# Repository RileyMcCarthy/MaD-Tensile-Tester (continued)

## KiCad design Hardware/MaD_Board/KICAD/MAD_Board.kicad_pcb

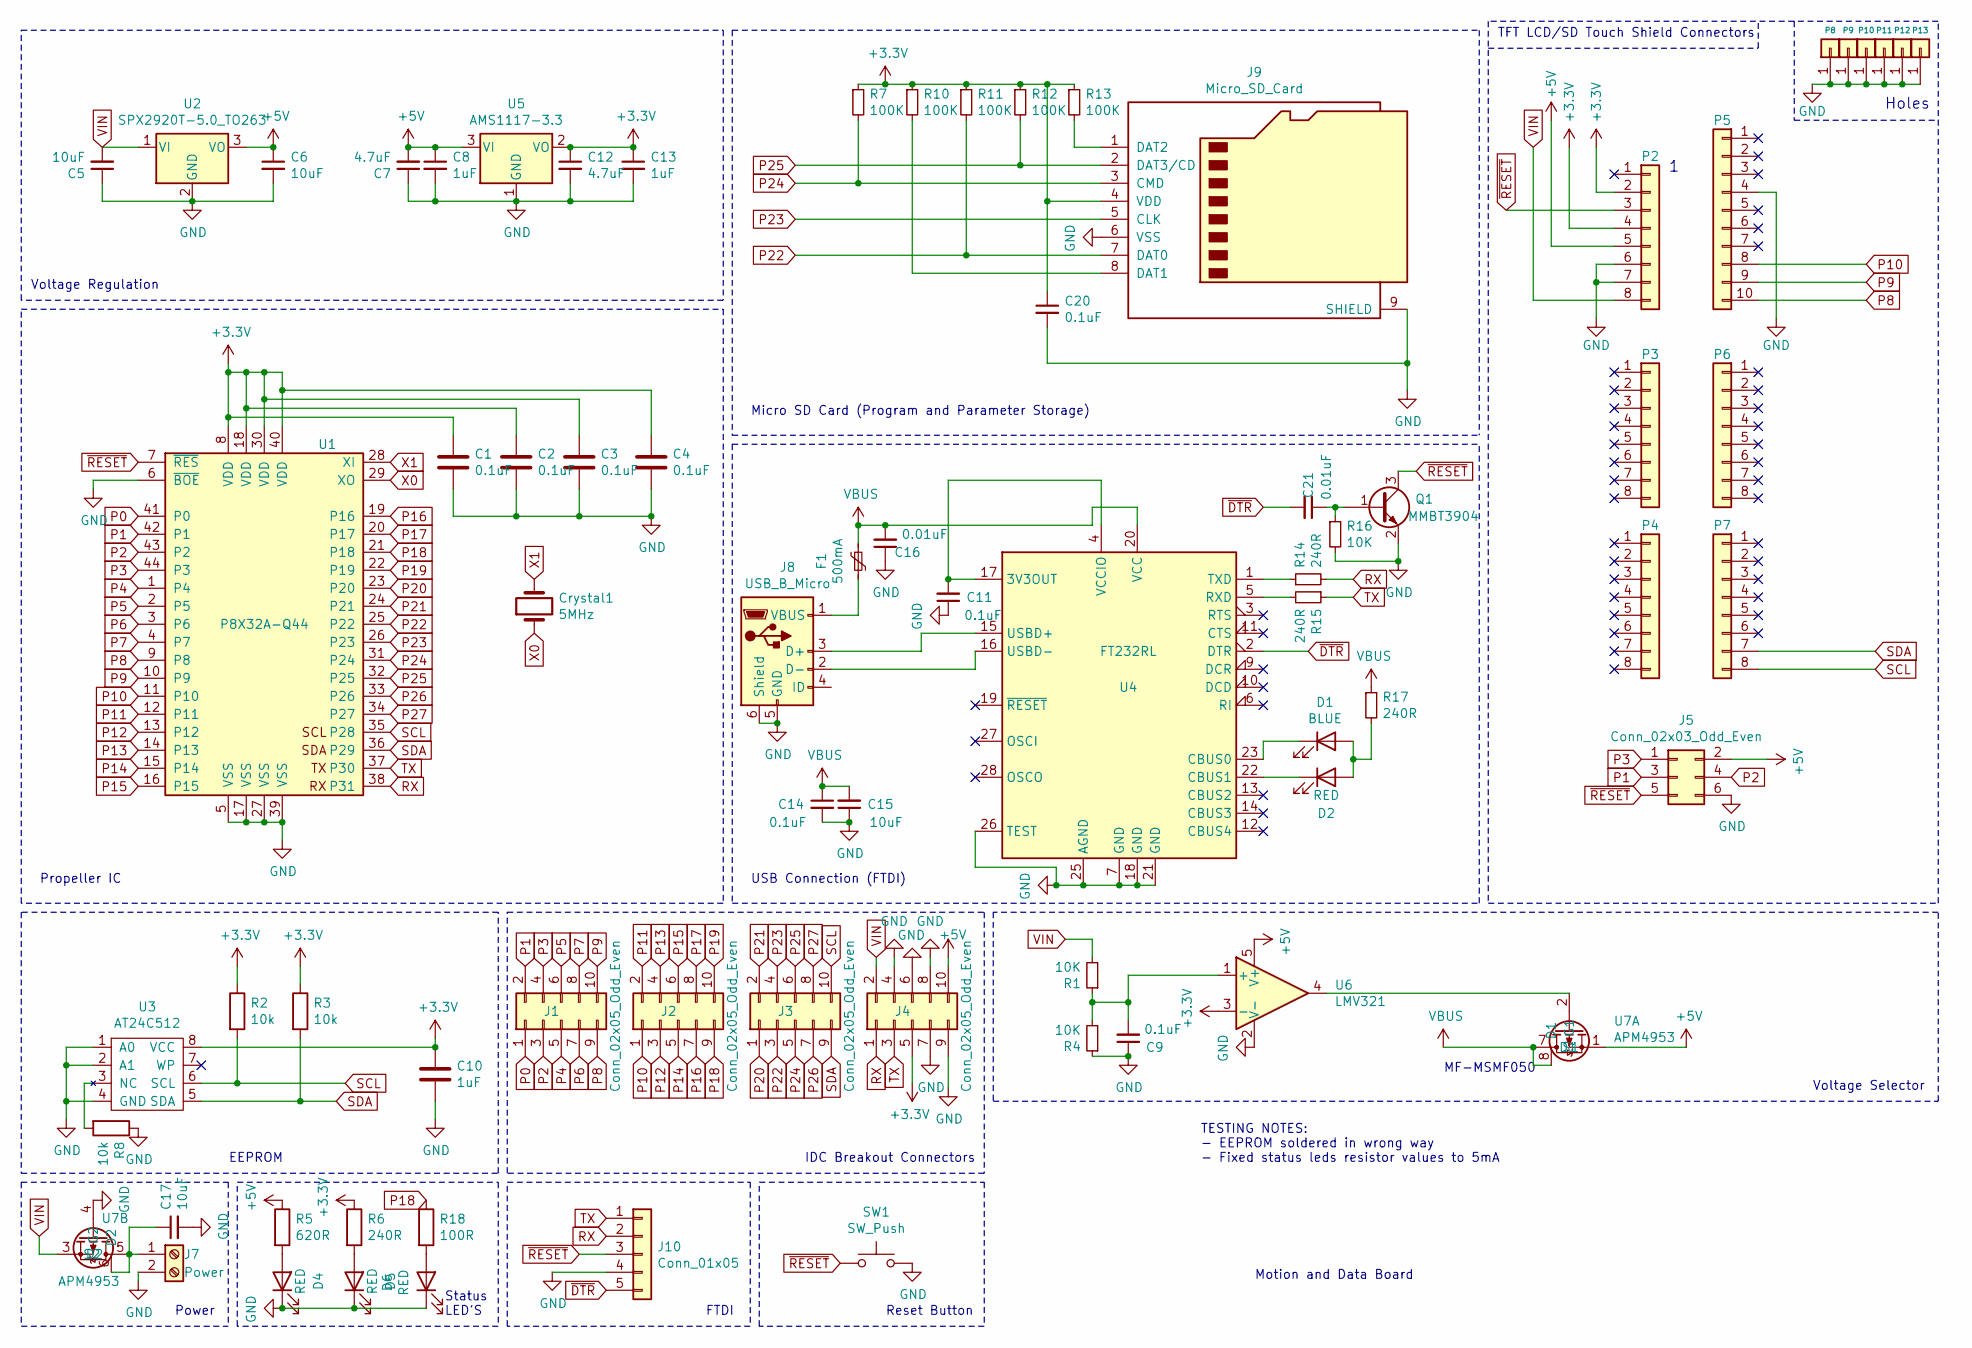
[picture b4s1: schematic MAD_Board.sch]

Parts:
C1, C2, C3, C4, C9, C11, C14, C20: 0.1uF; C_0603_1608Metric; LCSC Part # C14663
C5, C6, C15, C17: 10uF; C_0805_2012Metric; LCSC Part # C15850
C7, C12: 4.7uF; C_0603_1608Metric; LCSC Part # C14663
C8, C10, C13: 1uF; C_0603_1608Metric; LCSC Part # C15849
C16, C21: 0.01uF; C_0603_1608Metric; LCSC Part # C57112
Crystal1: 5MHz; Crystal_HC49-U_Vertical; LCSC Part # C2198
D1: BLUE; LED_0603_1608Metric; LCSC Part # C72041
D2, D4, D5, D6: RED; LED_0603_1608Metric; LCSC Part # C84256
F1: 500mA; Fuse_0603_1608Metric; LCSC Part # C210356
J1, J2, J3, J4: Conn_02x05_Odd_Even; IDC-Header_2x05_P2.54mm_Vertical
J5: Conn_02x03_Odd_Even; PinHeader_2x03_P2.54mm_Vertical
J7: Power; TerminalBlock_bornier-2_P5.08mm
J8: USB_B_Micro; USB_Micro-AB_Molex_47590-0001; LCSC Part # C404969
J9: Micro_SD_Card; microSD_HC_Hirose_DM3D-SF; LCSC Part # C719027
J10: Conn_01x05; PinHeader_1x05_P2.54mm_Vertical
P2: Power; Socket_Strip_Arduino_1x08
P3, P4: Analog; Socket_Strip_Arduino_1x08
P5: PWM; Socket_Strip_Arduino_1x10
P6: PWM; Socket_Strip_Arduino_1x08
P7: Communication; Socket_Strip_Arduino_1x08
P8, P9, P10, P11, P12, P13: CONN_01X01; Arduino_1pin
Q1: MMBT3904; SOT-23; LCSC Part # C20526
R1, R4, R16: 10K; R_0603_1608Metric; LCSC Part # C25804
R2, R3, R8: 10k; R_0603_1608Metric; LCSC Part # C25804
R5: 620R; R_0603_1608Metric; LCSC Part # C23220
R6, R14, R15, R17: 240R; R_0603_1608Metric; LCSC Part # C25221
R7, R10, R11, R12, R13: 100K; R_0603_1608Metric; LCSC Part # C25803
R18: 100R; R_0603_1608Metric; LCSC Part # C22775
SW1: SW_Push; LED_1210_3225Metric
U1: P8X32A-Q44; LQFP-44_10x10mm_P0.8mm
U2: SPX2920T-5.0_TO263; TO-263-3_TabPin2; LCSC Part # C24592
U3: AT24C512; SOIC-8-1EP_3.9x4.9mm_P1.27mm_EP2.514x3.2mm; LCSC Part # C6482
U4: FT232RL; SSOP-28_5.3x10.2mm_P0.65mm; LCSC Part # C8690
U5: AMS1117-3.3; SOT-223-3_TabPin2; LCSC Part # C6186
U6: LMV321; SOT-23-5; LCSC Part # C7972
U7: APM4953; SOP-8_3.9x4.9mm_P1.27mm; LCSC Part # C20897

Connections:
+3V3: C1.1, C2.1, C3.1, C4.1, C10.1, C12.1, C13.1, C20.1, J4.5, J9.4 (VDD), P2.2, P2.4, R2.1, R3.1, R6.1, R7.1, R10.1, R11.1, R12.1, R13.1, U1.8 (VDD), U1.18 (VDD), U1.30 (VDD), U1.40 (VDD), U3.8 (VCC), U5.2 (VO), U6.3 (-)
+5V: C6.1, C7.2, C8.1, J4.10, J5.2, P2.5, R5.1, U2.3 (VO), U5.3 (VI), U6.5 (V+), U7.1 (S1)
GND: C1.2, C2.2, C3.2, C4.2, C5.1, C6.2, C7.1, C8.2, C9.1, C10.2, C11.1, C12.2, C13.2, C14.2, C15.1, C16.1, C17.2, C20.2, D4.1 (K), D5.1 (K), D6.1 (K), J4.4, J4.6, J4.7, J4.8, J4.9, J5.6, J7.2, J8.5 (GND), J8.6 (Shield), J9.6 (VSS), J9.9 (SHIELD), J10.4, P2.6, P2.7, P5.4, P8.1, P9.1, P10.1, P11.1, P12.1, P13.1, Q1.2 (E), R4.1, R8.1, R16.2, SW1.2, U1.5 (VSS), U1.6 (~BOE), U1.17 (VSS), U1.27 (VSS), U1.39 (VSS), U2.2 (GND), U3.1 (A0), U3.2 (A1), U3.4 (GND), U4.7 (GND), U4.18 (GND), U4.21 (GND), U4.25 (AGND), U4.26 (TEST), U5.1 (GND), U6.2 (V-), U7.4 (G2)
unnamed: C9.2, R1.1, R4.2, U6.1 (+)
unnamed: C11.2, U4.4 (VCCIO), U4.17 (3V3OUT)
unnamed: C17.1, J7.1, U7.5 (D2), U7.6 (D2)
unnamed: C21.1, Q1.1 (B), R16.1
unnamed: D1.1 (K), U4.23 (CBUS0)
unnamed: D1.2 (A), D2.2 (A), R17.2
unnamed: D2.1 (K), U4.22 (CBUS1)
unnamed: D4.2 (A), R5.2
unnamed: D5.2 (A), R6.2
unnamed: D6.2 (A), R18.2
unnamed: F1.2, J8.1 (VBUS)
unnamed: J8.2 (D-), U4.16 (USBD-)
unnamed: J8.3 (D+), U4.15 (USBD+)
unnamed: J9.1 (DAT2), R13.2
unnamed: J9.8 (DAT1), R10.2
unnamed: R8.2, U3.3 (NC)
unnamed: R14.1, U4.1 (TXD)
unnamed: R15.2, U4.5 (RXD)
unnamed: U6.4, U7.2 (G1)
P0: J1.1, P6.8, U1.41 (P0)
P1: J1.2, J5.3, P6.7, U1.42 (P1)
P2: J1.3, J5.4, P6.6, U1.43 (P2)
P3: J1.4, J5.1, P6.5, U1.44 (P3)
P4: J1.5, P6.4, U1.1 (P4)
P5: J1.6, P6.3, U1.2 (P5)
P6: J1.7, P6.2, U1.3 (P6)
P7: J1.8, P6.1, U1.4 (P7)
P8: J1.9, P5.10, U1.9 (P8)
P9: J1.10, P5.9, U1.10 (P9)
P10: J2.1, P5.8, U1.11 (P10)
P11: J2.2, P5.7, U1.12 (P11)
P12: J2.3, P5.6, U1.13 (P12)
P13: J2.4, P5.5, U1.14 (P13)
P14: J2.5, P5.2, U1.15 (P14)
P15: J2.6, P5.1, U1.16 (P15)
P16: J2.7, U1.19 (P16)
P17: J2.8, U1.20 (P17)
P18: J2.9, R18.1, U1.21 (P18)
P19: J2.10, U1.22 (P19)
P20: J3.1, U1.23 (P20)
P21: J3.2, U1.24 (P21)
P22: J3.3, J9.7 (DAT0), R11.2, U1.25 (P22)
P23: J3.4, J9.5 (CLK), U1.26 (P23)
P24: J3.5, J9.3 (CMD), R7.2, U1.31 (P24)
P25: J3.6, J9.2 (DAT3/CD), R12.2, U1.32 (P25)
P26: J3.7, U1.33 (P26)
P27: J3.8, U1.34 (P27)
RX: J4.1, J10.2, R14.2, U1.38 (P31)
SCL: J3.10, P7.8, R2.2, U1.35 (P28), U3.6 (SCL)
SDA: J3.9, P7.7, R3.2, U1.36 (P29), U3.5 (SDA)
TX: J4.3, J10.1, R15.1, U1.37 (P30)
VBUS: C14.1, C15.2, C16.2, F1.1, R17.1, U4.20 (VCC), U7.7 (D1), U7.8 (D1)
VSS: C5.2, J4.2, P2.8, R1.2, U2.1 (VI), U7.3 (S2)
X0: Crystal1.1, U1.29 (XO)
X1: Crystal1.2, U1.28 (XI)
~DTR: C21.2, J10.5, U4.2 (DTR)
~RESET: J5.5, J10.3, P2.3, Q1.3 (C), SW1.1, U1.7 (~RES)

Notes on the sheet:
Holes
EEPROM
Propeller IC
USB Connection (FTDI)
Power
IDC Breakout Connectors
TFT LCD/SD Touch Shield Connectors
Motion and Data Board
MF-MSMF050
Voltage Selector
Micro SD Card (Program and Parameter Storage)
Voltage Regulation
FTDI
Reset Button
Status LED'S
TESTING NOTES: - EEPROM soldered in wrong way - Fixed status leds resistor values to 5mA

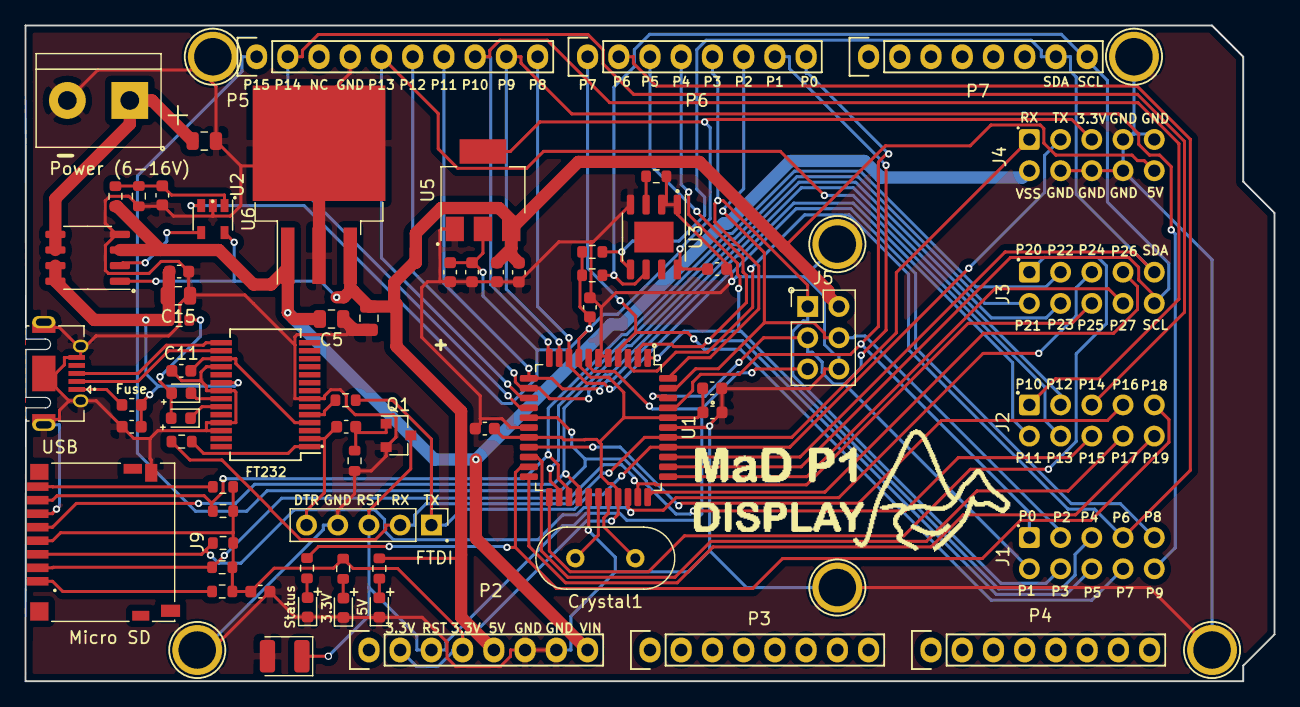
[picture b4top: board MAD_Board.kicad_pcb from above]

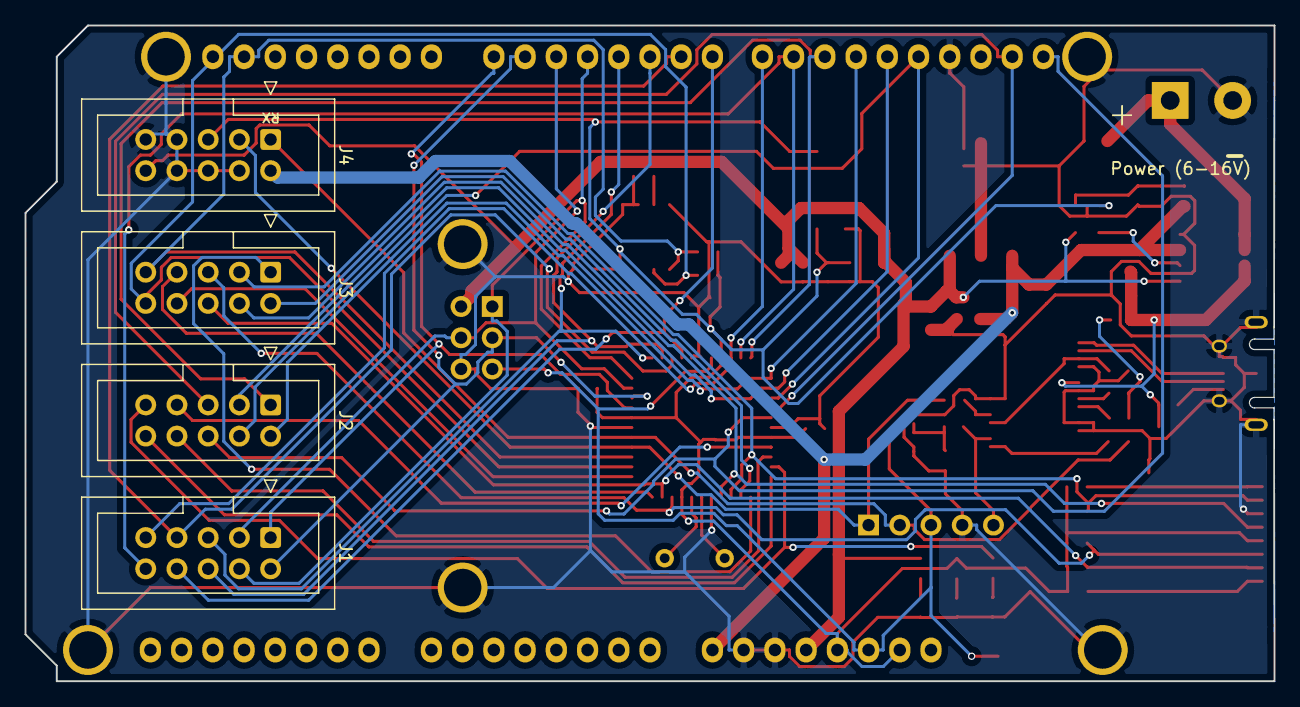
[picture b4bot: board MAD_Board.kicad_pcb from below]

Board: 2 copper layers, 101.6 x 53.3 mm, 74 parts (4 on the bottom side), 60 nets.

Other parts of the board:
LOGO: LOGO9

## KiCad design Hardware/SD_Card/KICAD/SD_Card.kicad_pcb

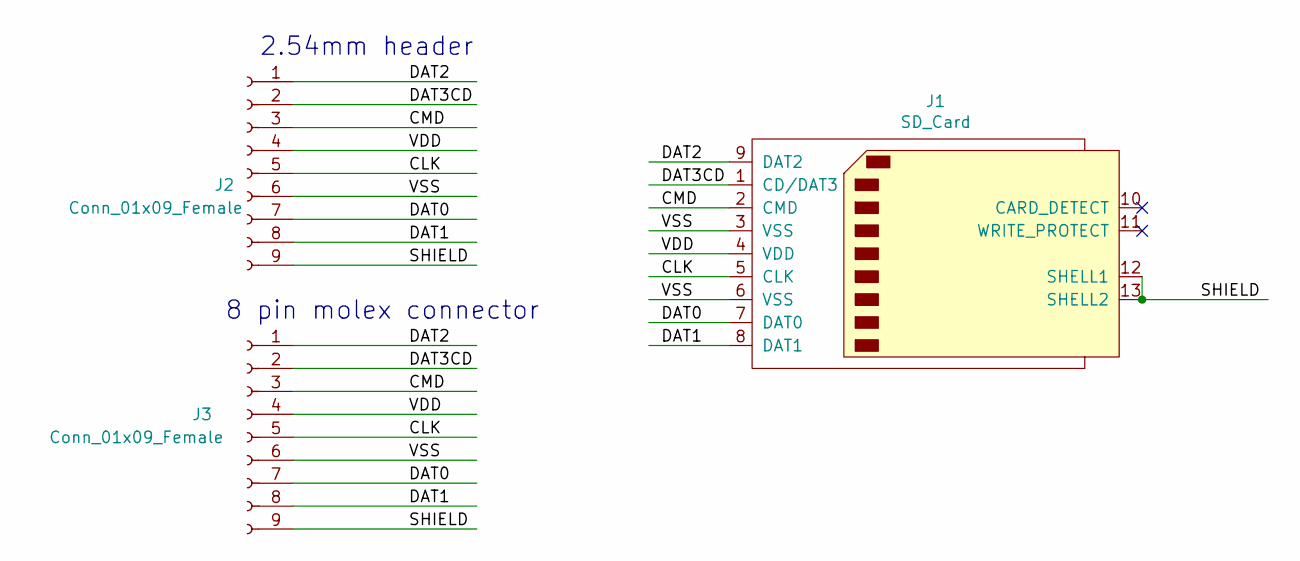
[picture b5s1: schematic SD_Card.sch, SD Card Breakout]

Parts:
J1: SD_Card; 609-3956-2-ND
J2: Conn_01x09_Female; WM26501
J3: Conn_01x09_Female; PinHeader_1x09_P2.54mm_Vertical

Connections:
/CLK: J1.5 (CLK), J2.5, J3.5
/CMD: J1.2 (CMD), J2.3, J3.3
/DAT0: J1.7 (DAT0), J2.7, J3.7
/DAT1: J1.8 (DAT1), J2.8, J3.8
/DAT2: J1.9 (DAT2), J2.1, J3.1
/DAT3CD: J1.1 (CD/DAT3), J2.2, J3.2
/SHIELD: J1.12 (SHELL1), J1.13 (SHELL2), J2.9, J3.9
/VDD: J1.4 (VDD), J2.4, J3.4
/VSS: J1.3 (VSS), J1.6 (VSS), J2.6, J3.6

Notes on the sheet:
2.54mm header
8 pin molex connector

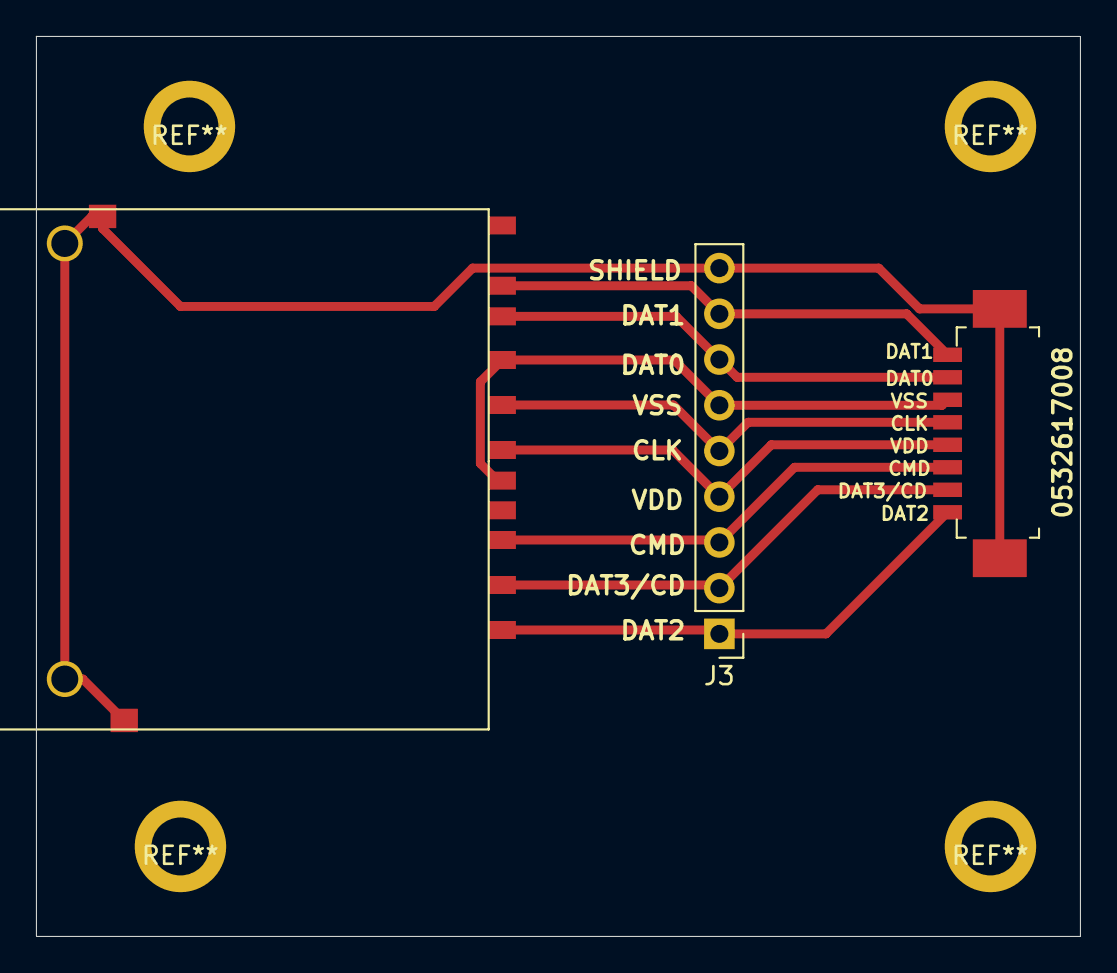
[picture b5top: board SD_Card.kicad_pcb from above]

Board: 2 copper layers, 58.0 x 50.0 mm, 3 parts (0 on the bottom side), 9 nets.

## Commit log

2021-04-02 init commit
2021-04-17 Merging all tensile testing machine related repositorys into a single repo
2021-04-18 Added MaD Firmware to repo
2021-04-24 Updated MaD_Firmware with demo code, issues with stack overflow will be updating soon
2021-04-24 Updated MaD_Firmware with demo code.Has some issues with stack overflow
2021-04-24 Updated MaD_Firmware with demo. Current contains stack overflow issues
2021-04-26 Updating comments
2021-04-27 Removed duplicate Tensile Board folder
2021-04-27 change state machine from c++ to c
2021-04-29 using libpropeller for forcegauge
2021-04-29 Updating force gauge with custom serial library
2021-04-29 Updating motion cog with access to machine state, and added some comments
2021-04-29 Fixed polarity issue with Tensile board
2021-04-29 added some comments:
2021-04-29 testi
2021-05-03 started changing LDO's to buck regulators
2021-05-04 Fixed read bug in force gauge library
2021-05-05 groundwork for p2
2021-05-06 Created power system for the MAD_P2 board, using evaluation board as reference
2021-05-07 Added memory and usb to schematic
2021-05-08 Added wifi to board
2021-05-10 added adc
2021-05-10 changed adc to ads131
2021-05-10 finished adc, added dac
2021-05-12 began pcb layout
2021-05-13 completed power section of board
2021-05-17 finished board layout
2021-05-17 added lcsc part numbers to bom
2021-05-20 replaced ads131E with ads131A
2021-05-21 added optional sd card socket for data
2021-05-21 revising pcb layout
2021-05-22 finished power supply board layout
2021-05-22 begining layout of adc/dac
2021-05-23 general layout complete
2021-05-24 routing power section
2021-05-27 routed adc
2021-05-27 test
2021-05-28 finished routing ground plane
2021-06-04 changed to 4 layer board due to number of wires to route. Routed ground and power nets
2021-06-05 fixed DAC issue and added silkscreen
2021-06-07 pushing updates before big change
2021-06-21 fully routed board, incorrect edge module pinout
2021-06-21 begining autorouter, had to start again after edge connector footprint was incorrect
2021-06-21 added boarders along keep out zones for autorouter:
2021-06-21 added keepout areas to adc/dac
2021-06-21 added silkscreen
2021-06-22 errors with connections to edge module fixed, created new dsn for autorouting
2021-06-22 re-routed power lines to edge module for optimized routes
2021-06-24 backup push before dsn import
2021-06-24 still waiting for freerouter to finish, completed silkscreen
2021-06-29 completed BOM with digikey and LSCS parts
2021-06-29 Finished re-routing the power and important connections. exported dsn for this stage of routing. running autorouter, may have few more commits before finished route
2021-07-03 board complete, exporting production files
2021-07-05 updated bom with lcsc part #
2021-08-06 Big update! All code is converted to the propeller 2 (mostly it compiles, many protocols needs conversion i2c,spi,ect). JSON library has gotten complete overhaul, now Machine Profiles can be transfer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
2021-08-09 added more functionality to JSON for motion quartet, motion set, motion profiles, machine profile, and more
2021-08-10 modified some json functionality
2021-08-10 adding windows copy of makefile while transferring to linux system
2021-08-12 completed JSON parsing library, still need to validate for memory leaks
2021-08-12 JSON library has all tests passing using larger heap size of 32768. I also added leak detection library which is not currently enabled in the makefile, next step is to run that
2021-08-12 Modified memory checking library to include realloc, also changed filename to function name to save space. Current commit has memory check disabled in makefile with all JSON checks working.
2021-08-13 memory leak detection working with all JSON tests running and no leaks, can view the amount of bytes currently allocated
2021-08-19 SD card test function is created and working
2021-08-20 DS3231 is now communicating with modified simplei2c library
2021-09-08 Converted JSON functionality to use files as storage instead of memory, this is due to large json files creating a stack overflow. SD card now uses folders for more organized storage
2021-09-11 display running properly, touch functionality temporarly not working... either code or EMI from bad header connectio
2021-09-12 converting pages to c
2021-09-23 changed serial library to P2 compatible library
2021-09-23 changed to arduino library for MCP23017 converted to P2 using modified i2c lib
2021-09-23 minor changes
2021-09-23 converting pages from c++ to c, while updating syntax
2021-09-23 converting to c++
2021-10-09 communication with dyn4 working. Reading encoder using spin2 object from obex
2021-11-11 major update
2021-11-11 minon changes
2021-11-11 created images for display
2021-11-11 added status page image
2021-12-01 working on force gauge
2021-12-06 created new images for display: calibration and files
2021-12-06 removed vscode folder, non needed in repo
2021-12-06 added new page Calibrate Force page
2021-12-09 Update Keyboard.h
    fixed keyboard object to use dynamic memory instead of static, may be reverted
2021-12-09 Update MaD.h
    changed to run without machine profile loading from sd card
2021-12-09 updated pages to use dynamic image object
2021-12-09 minor fixes
2021-12-19 minor bug fixes
2021-12-19 system functioning, issue while parsing json file to structure casuing system to crash. Will replace with CJSON
2021-12-19 adding cJSON library to parse json files
2021-12-19 cleanup
2021-12-19 added cJSON contents
2021-12-22 bringing repo up to date
2021-12-31 set/get pin functions set direction also
2021-12-31 Modified machine states to better fit documentation
2022-01-06 video demo state
2022-01-12 added settings
2022-01-16 working on state machine
2022-01-24 syncing info
2022-01-24 minor warning fixes
2022-04-06 big update
2022-04-13 latest version
2022-04-24 added commenting
2022-05-04 fixed file reading and writing
2022-05-06 refactoring status page to utilize modules
2022-05-06 fixed bug while storing slope in N instead of mN
2022-05-10 converting status page to modules
2022-05-11 Changing windows as modules
2022-05-14 Developing dynamic module updating system
2022-05-14 implemented dynamic text align and dynamic updating of windows
2022-05-18 implementing graphs on status page
2022-05-19 added title, units, and scale to graphs
2022-05-26 working state
2022-05-27 commit prev to converting to static memory allocation
2022-05-27 converted MaD.c to static memory, JSON library needs modifications next
2022-06-03 continuing static memory conversion
2022-06-27 UI overhaul
2022-06-29 continuing major UI update
2022-07-14 backing up before upddate
2022-07-14 modified header files to use fromfile to compile using flexspin
2022-07-15 testing flash functioning
2022-08-06 partial working status, beginning to work on sim
2022-08-06 compiling state before sim
2022-08-07 working on windows sim
2022-08-07 cleaning repo
2022-08-07 more cleaning
2022-08-07 translating settings page to new UI
2022-08-16 before switch to serial
2022-08-18 backup
2022-08-18 cleaning repo before big changes
2022-08-18 working test sendind structures over serial as binary
2022-08-18 communicating using comands in binary
2022-08-22 Major cleaning of gui related functions, conversion to serial comm for rpi
2022-08-25 working initialization of serial comm
2022-09-07 saving before big update
2022-10-02 using flask web interface
2022-10-05 before removing csrf token
2022-10-05 stashing current version before modifying motion planning
2022-10-06 working version before usb comb
2022-11-10 before removing flash
2022-11-11 working on implementing spi thread
2022-11-18 getting data using spi
2022-11-18 writing data to file
2022-11-22 new documentation for installation
2022-11-22 fixed readme
2022-11-24 before changing json for FunctionInfo
2022-11-24 before removing spi
2022-11-30 before using packets
2022-12-02 partially working state
2022-12-22 moving website to /Software
2022-12-22 moving web to /Software
2023-01-12 push before removing motion profiles
2023-01-12 removed dyn4 library and removed motion profiles
2023-02-17 before remving sd card flexibility
2023-03-23 Large update
2023-04-28 cleaning up repo
2023-04-28 more files to clean
2023-04-28 Remove ignored files
2023-05-06 cleaning old hardware, new Mad_Edge to replace them
2023-06-06 new Mad Edge being manufactured
2023-07-07 working version for getting basic data for the thesis
2023-07-07 working version, fixed force gauge and added gauge length, need to look into command_to_string() bug
2023-07-19 issues with loading profiles, might be due to connector. last commit might be more stable
2023-07-24 updating gitignore to remove backups for kicad
2023-07-25 cleaning up production files
2023-07-25 Adding workflow and gitignore
2023-07-26 developing notifications for website
2023-07-27 motion profile page
2023-07-31 working
2023-08-01 Saving data for rpi reset
2023-08-08 Saving before end of work day
2023-08-11 uploading profiles and viewing is working
2023-08-15 hot swappable sd card and headers for tests
2023-08-15 moving firmware to submodule
2023-08-15 moving website to submodule
2023-08-15 moving mad edge to submodule
2023-08-15 moving ds2 addon to submodule
2023-08-15 moving power board to submodule
2023-08-15 updating submodules to track master
2023-08-15 updating submodules
2023-08-23 fix firmware bug
